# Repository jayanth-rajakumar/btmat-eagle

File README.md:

# btmat-eagle
Eagle schematic for the btmat board to interface stackmat timers and Android phones via bluetooth.

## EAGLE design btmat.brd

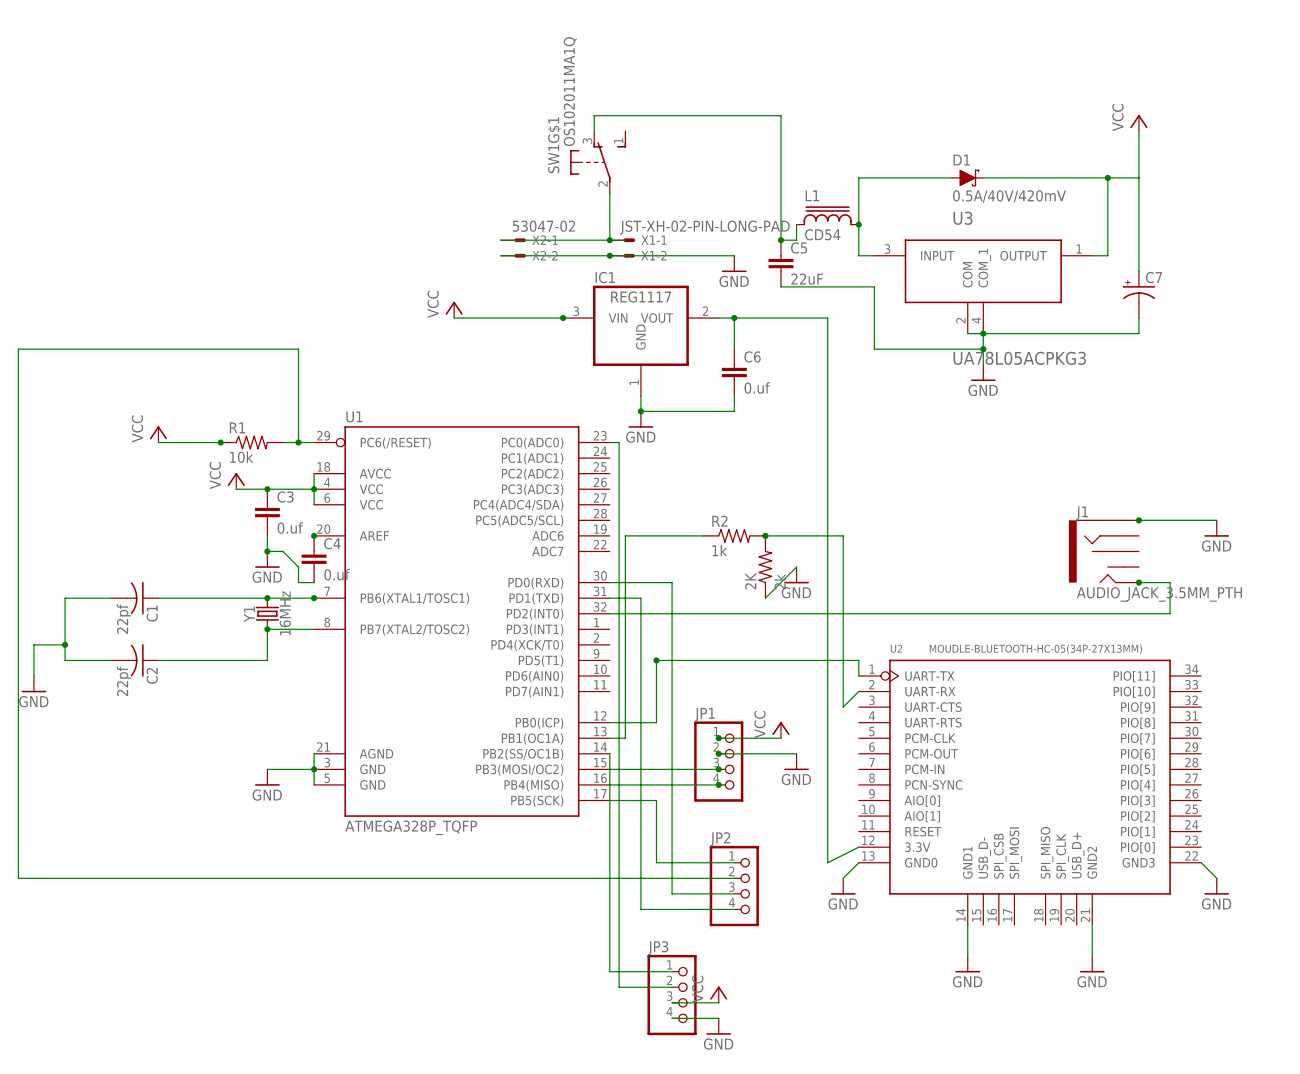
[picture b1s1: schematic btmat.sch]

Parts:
2K: 2k; R0805
C1, C2: 22pf; C0805
C3, C4, C6: 0.uf; C0805
C5: 22uF; C0805
C7: CPOL-USC/6032-28R; C/6032-28R
D1: 0.5A/40V/420mV; SOD-323
IC1: REG1117; SOT223
J1: AUDIO_JACK_3.5MM_PTH; AUDIO-JACK
JP1, JP2, JP3: PINHD-1X4; 1X04
L1: CD54
R1: 10k; R0805
R2: 1k; R0805
SW1: OS102011MA1Q
U1: ATMEGA328P_TQFP; TQFP32-08
U2: MOUDLE-BLUETOOTH-HC-05(34P-27X13MM); BT34P-SMD-1.5-26.9X13.0X2.2MM
U3: UA78L05ACPKG3; SOT150P400X160-4N
X1: JST-XH-02-PIN-LONG-PAD; JST-XH-02-PACKAGE-LONG-PAD
X2: 53047-02
Y1: 16MHz; HC49US

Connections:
GND: 2K.1, C1.2, C2.2, C3.2, C4.2, C5.2, C6.2, C7.-, IC1.1 (GND), J1.SLEEVE, JP1.2, JP3.4, U1.3 (GND), U1.5 (GND), U1.21 (AGND), U2.13 (GND0), U2.14 (GND1), U2.21 (GND2), U2.22 (GND3), U3.2 (COM), U3.4 (COM_1), X1.2, X2.2
unnamed: C2.1, U1.8 (PB7(XTAL2/TOSC2)), Y1.1
unnamed: C1.1, U1.7 (PB6(XTAL1/TOSC1)), Y1.2
unnamed: JP2.2, R1.2, U1.29 (PC6(/RESET))
unnamed: C6.1, IC1.2 (VOUT), U2.12 (3.3V)
unnamed: JP1.4, U1.16 (PB4(MISO))
unnamed: JP1.3, U1.15 (PB3(MOSI/OC2))
unnamed: JP2.1, U1.17 (PB5(SCK))
unnamed: U1.12 (PB0(ICP)), U2.1 (UART-TX)
unnamed: JP2.4, U1.31 (PD1(TXD))
unnamed: JP2.3, U1.30 (PD0(RXD))
unnamed: D1.A, L1.2, U3.3 (INPUT)
unnamed: C5.1, L1.1, SW1.3 (O)
unnamed: 2K.2, R2.2, U2.2 (UART-RX)
unnamed: SW1.2, X1.1, X2.1
unnamed: R2.1, U1.13 (PB1(OC1A))
unnamed: C4.1, U1.20 (AREF)
unnamed: J1.TIP, U1.32 (PD2(INT0))
unnamed: JP3.2, U1.23 (PC0(ADC0))
unnamed: JP3.1, U1.14 (PB2(SS/OC1B))
VCC: C3.1, C7.+, D1.C, IC1.3 (VIN), JP1.1, JP3.3, R1.1, U1.4 (VCC), U1.6 (VCC), U1.18 (AVCC), U3.1 (OUTPUT)

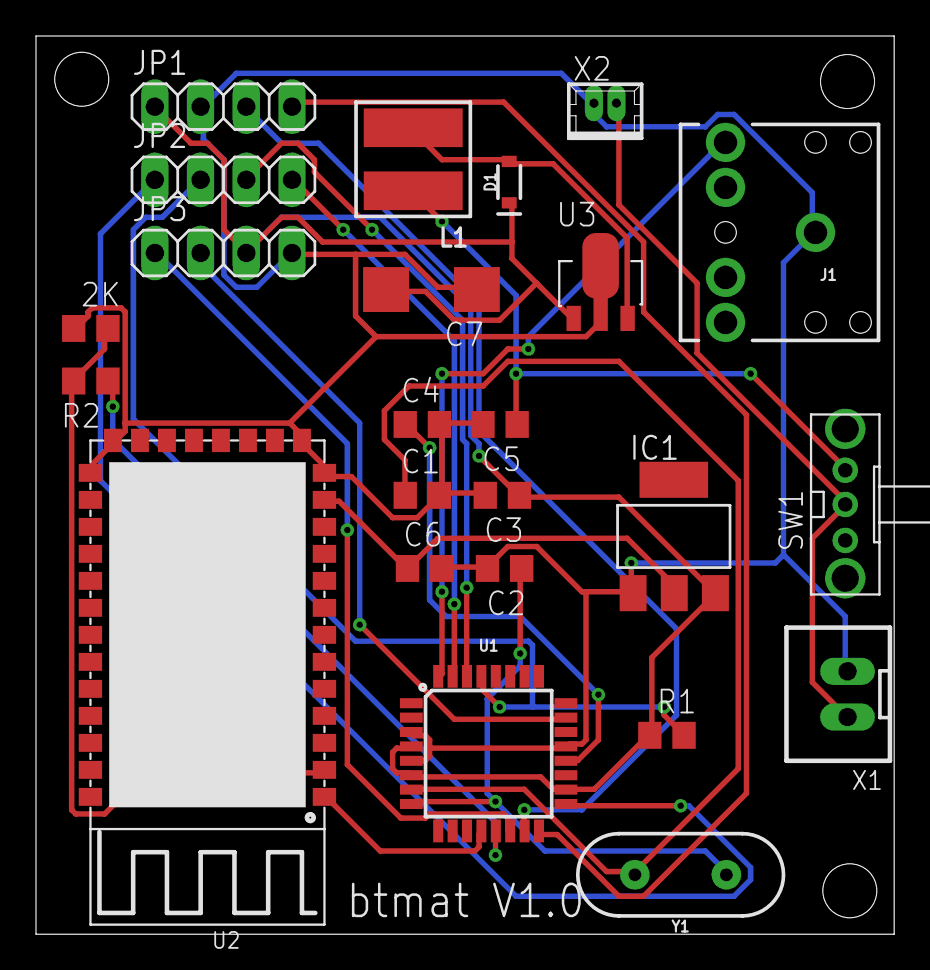
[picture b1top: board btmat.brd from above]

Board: 2 copper layers, 47.7 x 49.9 mm, 24 parts (0 on the bottom side), 21 nets.

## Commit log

2018-01-15 Added eagle files
2018-01-15 Added image to readme
2018-01-15 Added prototype image

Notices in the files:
parts and their libraries:
SparkFun-Connectors: Licensing: Creative Commons ShareAlike 4.0 International - https://creativecommons.org/licenses/by-sa/4.0
inductor-sumida: Copyright (C) 2008, Bob Starr
